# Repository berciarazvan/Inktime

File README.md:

# InkTime

## Prezentarea proiectului

InkTime este un smartwatch open-source, cu cost redus, construit in jurul platformei nRF52840. Proiectul urmeaza cerinta din cadrul cursului de a duce produsul de la stadiul de proiectare electronica pana la o versiune care poate fi fabricata, asamblata si verificata mecanic in carcasa oferita. Repository-ul curent contine schema electrica, layout-ul PCB-ului, fisierele de fabricatie si integrarea 3D necesara pentru etapa EVT.

Designul combina comunicatie wireless, incarcare pentru baterie, monitorizarea bateriei, detectarea miscarii, feedback haptic si interfata pentru un display e-paper pe o placa compacta, adaptata formei carcasei ceasului. Placa a fost dezvoltata ca o solutie pe doua straturi, cu componentele principale plasate pe stratul superior, iar integrarea mecanica a fost verificata in Fusion folosind modelul de carcasa pus la dispozitie.

## Diagrama bloc

```mermaid
flowchart LR
    USB[Conector USB-C] --> ESD[Protectie ESD pentru USB]
    ESD --> CHG[BQ25180 incarcare si management alimentare]
    BAT[Baterie Li-Po] --> CHG
    CHG --> FG[MAX17048 monitorizare baterie]
    CHG --> DCDC[RT6160 convertor buck-boost]
    DCDC --> PWR[Linie principala de 3.3 V]

    PWR --> MCU[nRF52840 microcontroller]
    MCU --> ANT[Antena 2.4 GHz]
    MCU --> IMU[Accelerometru BMA42x]
    MCU --> HAPTIC[Driver haptic DRV2605]
    HAPTIC --> MOTOR[Motor vibratie]
    MCU --> BTN[Trei butoane utilizator]
    MCU --> EPDIF[Interfata logica e-paper]
    EPDIF --> EPDRV[Etaj de comanda e-paper]
    EPDRV --> EPD[Display e-paper]
    MCU --> SWD[Pad-uri programare SWD]
    FG --> MCU
    CHG --> MCU
```

## Bill of Materials

Tabelul de mai jos reprezinta un BOM scurt inclus in README. Fisierele complete pentru fabricatie si asamblare se gasesc in folderul `Manufacturing`. Pentru claritate, tabelul pune accent pe componentele principale si nu pe toate componentele pasive de pe placa.

| Designator | Componenta | Rol in proiect | Link JLC / achizitie | Datasheet |
|---|---|---|---|---|
| U1 | nRF52840-QIAA-R | Microcontroller principal si platforma wireless | [JLCPCB](https://jlcpcb.com/partdetail/NordicSemicon-NRF52840_QIAAR/C190794) | [Nordic Product Specification](https://docs.nordicsemi.com/bundle/nRF52840_PS_v1.9/resource/nRF52840_PS_v1.9.pdf) |
| IC1 | BQ25180YBGR | Incarcator pentru baterie Li-Po si management de alimentare | [JLCPCB](https://jlcpcb.com/partdetail/C3682423) | [Texas Instruments](https://www.ti.com/lit/gpn/BQ25180) |
| IC9 | RT6160AWSC | Convertor buck-boost pentru generarea liniei principale de 3.3 V | [JLCPCB](https://jlcpcb.com/partdetail/C7065276) | [Richtek](https://www.richtek.com/assets/product_file/RT6160A/DS6160A-05.pdf) |
| U3 | MAX17048G+T10 | Circuit de monitorizare a nivelului bateriei | [JLCPCB](https://jlcpcb.com/partdetail/MaximIntegrated-MAX17048GT10/C2682616) | [Analog Devices](https://www.analog.com/media/en/technical-documentation/data-sheets/max17048-max17049.pdf) |
| IC3 | Bosch BMA42x | Accelerometru pentru detectarea miscarii | [JLCPCB search for BMA42x family](https://jlcpcb.com/partdetail/C5242966) | [BMA423 datasheet](https://watchy.sqfmi.com/assets/files/BST-BMA423-DS000-1509600-950150f51058597a6234dd3eaafbb1f0.pdf) |
| IC2 | DRV2605YZFR | Driver haptic pentru actuatorul de vibratie | [JLCPCB](https://jlcpcb.com/partdetail/TexasInstruments-DRV2605YZFR/C81079) | [Texas Instruments](https://www.ti.com/lit/ds/symlink/drv2605.pdf) |
| ANT1 | 2450AT18B100E | Antena chip de 2.4 GHz pentru sectiunea RF | [JLCPCB](https://jlcpcb.com/partdetail/JohansonTechnology-2450AT18B100/C2836414) | [Johanson Technology](https://www.johansontechnology.com/docs/1187/2450AT18B100_X8XXogU.pdf) |
| J4 | KH-TYPE-C-16P | Conector USB-C pentru incarcare si date USB | [JLCPCB](https://jlcpcb.com/partdetail/KH-TYPE-C-16P/C709357) | [Part page with downloadable datasheet](https://jlcpcb.com/partdetail/KH-TYPE-C-16P/C709357) |
| D3 | USBLC6-2SC6Y | Protectie ESD pentru liniile USB | [Reference part page](https://jlcpcb.com/partdetail/ElecSuper-SP2555NUTG_ES/C54533292) | [STMicroelectronics](https://www.st.com/resource/en/datasheet/usblc6-2sc6y.pdf) |
| J1 | 503480-2400 | Conector cu pas fin pentru display-ul e-paper | [Selected connector family](https://www.molex.com/en-us/products/part-detail/5034802400) | [Molex product page](https://www.molex.com/en-us/products/part-detail/5034802400) |
| J2 | TC2030-IDC | Conector extern pentru programare si depanare | [Tag-Connect](https://www.tag-connect.com/product/tc2030-idc-nl) | [Product page](https://www.tag-connect.com/product/tc2030-idc-nl) |

Bateria, panoul e-paper si actuatorul haptic fac de asemenea parte din produsul final, insa in repository-ul curent ele sunt tratate in principal ca elemente de integrare mecanica. Modelele lor 3D sunt incluse in lucrul de asamblare pentru a verifica dispozitivul complet in interiorul carcasei.

## Functionalitatea hardware

Nucleul sistemului este nRF52840, ales pentru ca se potriveste unui dispozitiv purtabil care are nevoie de consum redus, suport wireless integrat si suficiente interfete digitale pentru senzori, controlul display-ului si depanare. In jurul microcontroller-ului, designul pastreaza reteaua RF si antena aproape de marginea placii, iar condensatoarele de decuplare sunt amplasate aproape de pinii de alimentare pentru a mentine sursa stabila.

Sectiunea de alimentare porneste de la conectorul USB-C. Liniile USB sunt protejate de un circuit dedicat de protectie ESD inainte sa ajunga in restul circuitului. Incarcatorul BQ25180 gestioneaza alimentarea de intrare, incarca bateria cu o singura celula si ofera calea de alimentare necesara atunci cand este prezenta tensiunea de la USB. Starea bateriei este monitorizata de MAX17048, astfel incat firmware-ul sa poata estima nivelul de incarcare si sa afiseze aceasta informatie utilizatorului.

Pentru ca sistemul trebuie sa ramana stabil atat atunci cand functioneaza din USB, cat si atunci cand functioneaza din baterie, linia principala este generata de convertorul RT6160. Acest bloc creeaza tensiunea de 3.3 V folosita de partea logica a ceasului. Rezultatul este o alimentare mai stabila pentru microcontroller, senzor, driverul haptic si interfata display-ului.

Detectarea miscarii este realizata cu un accelerometru din familia Bosch BMA42x. Acest dispozitiv comunica cu microcontroller-ul prin magistrala seriala comuna si ofera si linii de intrerupere, ceea ce permite trezirea sistemului sau detectarea unor evenimente de miscare fara interogare continua.

Feedback-ul pentru utilizator este oferit in doua moduri. Primul este vizual, prin conectorul pentru display-ul e-paper si etajul dedicat de comanda al acestuia. Al doilea este tactil, prin driverul DRV2605, care controleaza actuatorul de vibratie. Driverul haptic este conectat pe aceeasi magistrala seriala folosita de celelalte periferice lente, iar un semnal separat de activare permite control clar din partea microcontroller-ului.

Zona dedicata e-paper include atat interfata logica, cat si etajul mic de comanda necesar panoului. Semnalele logice sunt generate de microcontroller, in timp ce etajul analogic extern creeaza tensiunile auxiliare cerute de display. Pe langa conectorul propriu-zis, placa include si un element de comutatie care permite activarea sau dezactivarea ramurii de alimentare a display-ului atunci cand este necesar pentru economisirea energiei.

Trei butoane de utilizator sunt plasate pe placa si aliniate cu butoanele laterale ale carcasei. Fiecare buton este conectat la o intrare dedicata si are o retea pasiva simpla pentru citire stabila. Programarea si depanarea sunt disponibile prin interfata SWD si prin test pad-uri marcate clar, ceea ce usureaza aducerea placii in functiune si validarea.

## Utilizarea pinilor nRF52840

Tabelul de mai jos rezuma principalele conexiuni vizibile in schema incarcata. Scopul acestei sectiuni este sa arate modul in care resursele microcontroller-ului au fost grupate astfel incat designul sa ramana simplu de rutat si usor de urmarit in review.

| Semnal MCU | Functia conectata | Motivul utilizarii |
|---|---|---|
| P0.06 | SDA pentru charger, accelerometru, fuel gauge si driver haptic | O magistrala comuna pentru control reduce complexitatea rutarii si lasa mai multi pini disponibili pentru display si butoane. |
| P0.07 | SCL pentru charger, accelerometru, fuel gauge si driver haptic | Acest pin completeaza magistrala comuna folosita de perifericele de control. |
| P0.08 | IMU interrupt 1 | Aceasta linie permite senzorului sa anunte microcontroller-ul atunci cand apare un eveniment legat de miscare. |
| P1.08 | IMU interrupt 2 | A doua linie de intrerupere ofera flexibilitate pentru functii viitoare si pentru trezire in mod de consum redus. |
| P0.10 | Alerta fuel gauge | Acest semnal poate informa firmware-ul despre evenimente legate de baterie fara interogare constanta. |
| P0.11 | Intrerupere charger | Starea incarcatorului poate fi observata direct de microcontroller, ceea ce ajuta la incarcare si la schimbarile de regim de alimentare. |
| P0.12 | Activare haptic | O linie dedicata ofera control direct asupra sectiunii haptice. |
| P0.02 | Clock serial pentru e-paper | Acest pin este folosit ca linie de ceas pentru interfata de date a display-ului. |
| P0.03 | Date seriale pentru e-paper | Acest pin transporta fluxul de date catre display. |
| P0.05 | Chip select pentru e-paper | Interfata display-ului este separata printr-un semnal dedicat de selectare. |
| P0.15 | Selectare date/comanda pentru e-paper | Aceasta linie diferentiaza comenzile de datele trimise display-ului. |
| P0.16 | Reset pentru e-paper | Display-ul poate fi reinitializat corect prin firmware. |
| P0.17 | Busy pentru e-paper | Microcontroller-ul poate astepta finalizarea operatiilor interne ale panoului inainte de o noua comanda. |
| P1.01 | Control comutare alimentare display | Acest pin comanda poarta MOSFET-ului care activeaza sau dezactiveaza alimentarea display-ului. |
| P0.13 | Intrare buton utilizator | Intrare digitala dedicata pentru unul dintre butoanele ceasului. |
| P0.14 | Intrare buton utilizator | Intrare digitala dedicata pentru unul dintre butoanele ceasului. |
| P1.02 | Intrare buton utilizator | Intrare digitala dedicata pentru al treilea buton al ceasului. |
| D+ / D- / VBUS | Interfata USB nativa | Aceste linii ofera conexiunea USB folosita pentru incarcare si posibila comunicatie pe fir. |
| SWDIO / SWDCLK / P1.00 | Programare si depanare | Aceste semnale permit incarcarea firmware-ului, depanarea si validarea prin SWD si test pad-uri. |

In acest design, liniile display-ului au fost pastrate separat de magistrala comuna de control, astfel incat calea de actualizare a imaginii sa ramana clara si directa. Magistrala comuna a fost rezervata pentru functiile suport, cum sunt incarcarea, monitorizarea bateriei, detectarea miscarii si controlul haptic, ceea ce reprezinta o impartire practica pentru o placa compacta de tip wearable.

## Integrarea PCB-ului si a partii mecanice

Forma PCB-ului urmeaza geometria carcasei si pastreaza antena spre marginea exterioara a placii. Cele trei butoane de utilizator sunt aliniate cu butoanele mecanice din carcasa, iar conectorul USB-C este pozitionat pe marginea placii pentru a ramane accesibil din exterior. Fisierele 3D din repository arata ca placa electronica a fost verificata impreuna cu carcasa pentru confirmarea potrivirii mecanice.

Capturile prezente in proiect pot fi introduse direct in README daca este nevoie. O imagine cu placa in 3D poate fi afisata cu ``, iar o vedere cu placa montata in carcasa poate fi afisata cu ``.

## Decizii de proiectare si observatii pentru review

Acest proiect a fost organizat astfel incat blocurile principale sa ramana usor de verificat in cadrul review-ului. Circuitul de alimentare a fost grupat compact, perifericele de control au fost plasate logic, iar zona RF a fost izolata aproape de marginea cu antena. Au fost adaugate test pad-uri pentru semnalele importante de alimentare si depanare, lucru util atat la aducerea in functiune, cat si in etapa de review.

O decizie practica in acest design a fost impartirea repository-ului in folderele `Hardware`, `Manufacturing`, `Mechanical` si `Images`, deoarece aceasta organizare urmeaza formatul cerut la curs si face proiectul mai usor de inspectat. O alta alegere importanta a fost pregatirea placii nu doar pentru verificare electrica, ci si pentru integrare in carcasa, deoarece validarea finala depinde atat de partea electrica, cat si de cea mecanica.

## Continutul repository-ului

Repository-ul este organizat conform cerintelor cursului. Folderul `Hardware` contine fisierele native pentru schema si PCB, impreuna cu exporturile PDF ale schemei. Folderul `Manufacturing` contine fisierele generate pentru fabricatie si asamblare. Folderul `Mechanical` contine lucrul de integrare in Fusion pentru ansamblul mecanic, iar folderul `Images` contine capturi care documenteaza layout-ul si integrarea in carcasa.

## Concluzie

InkTime este o platforma hardware compacta pentru un smartwatch, construita in jurul unui microcontroller cu consum redus, a unei arhitecturi de alimentare centrate pe baterie si a unui set complet de periferice potrivite pentru utilizare wearable. Versiunea actuala a proiectului include deja fisierele de design, iesirile pentru fabricatie si verificarile mecanice necesare pentru a continua spre validare, review si prezentarea finala.

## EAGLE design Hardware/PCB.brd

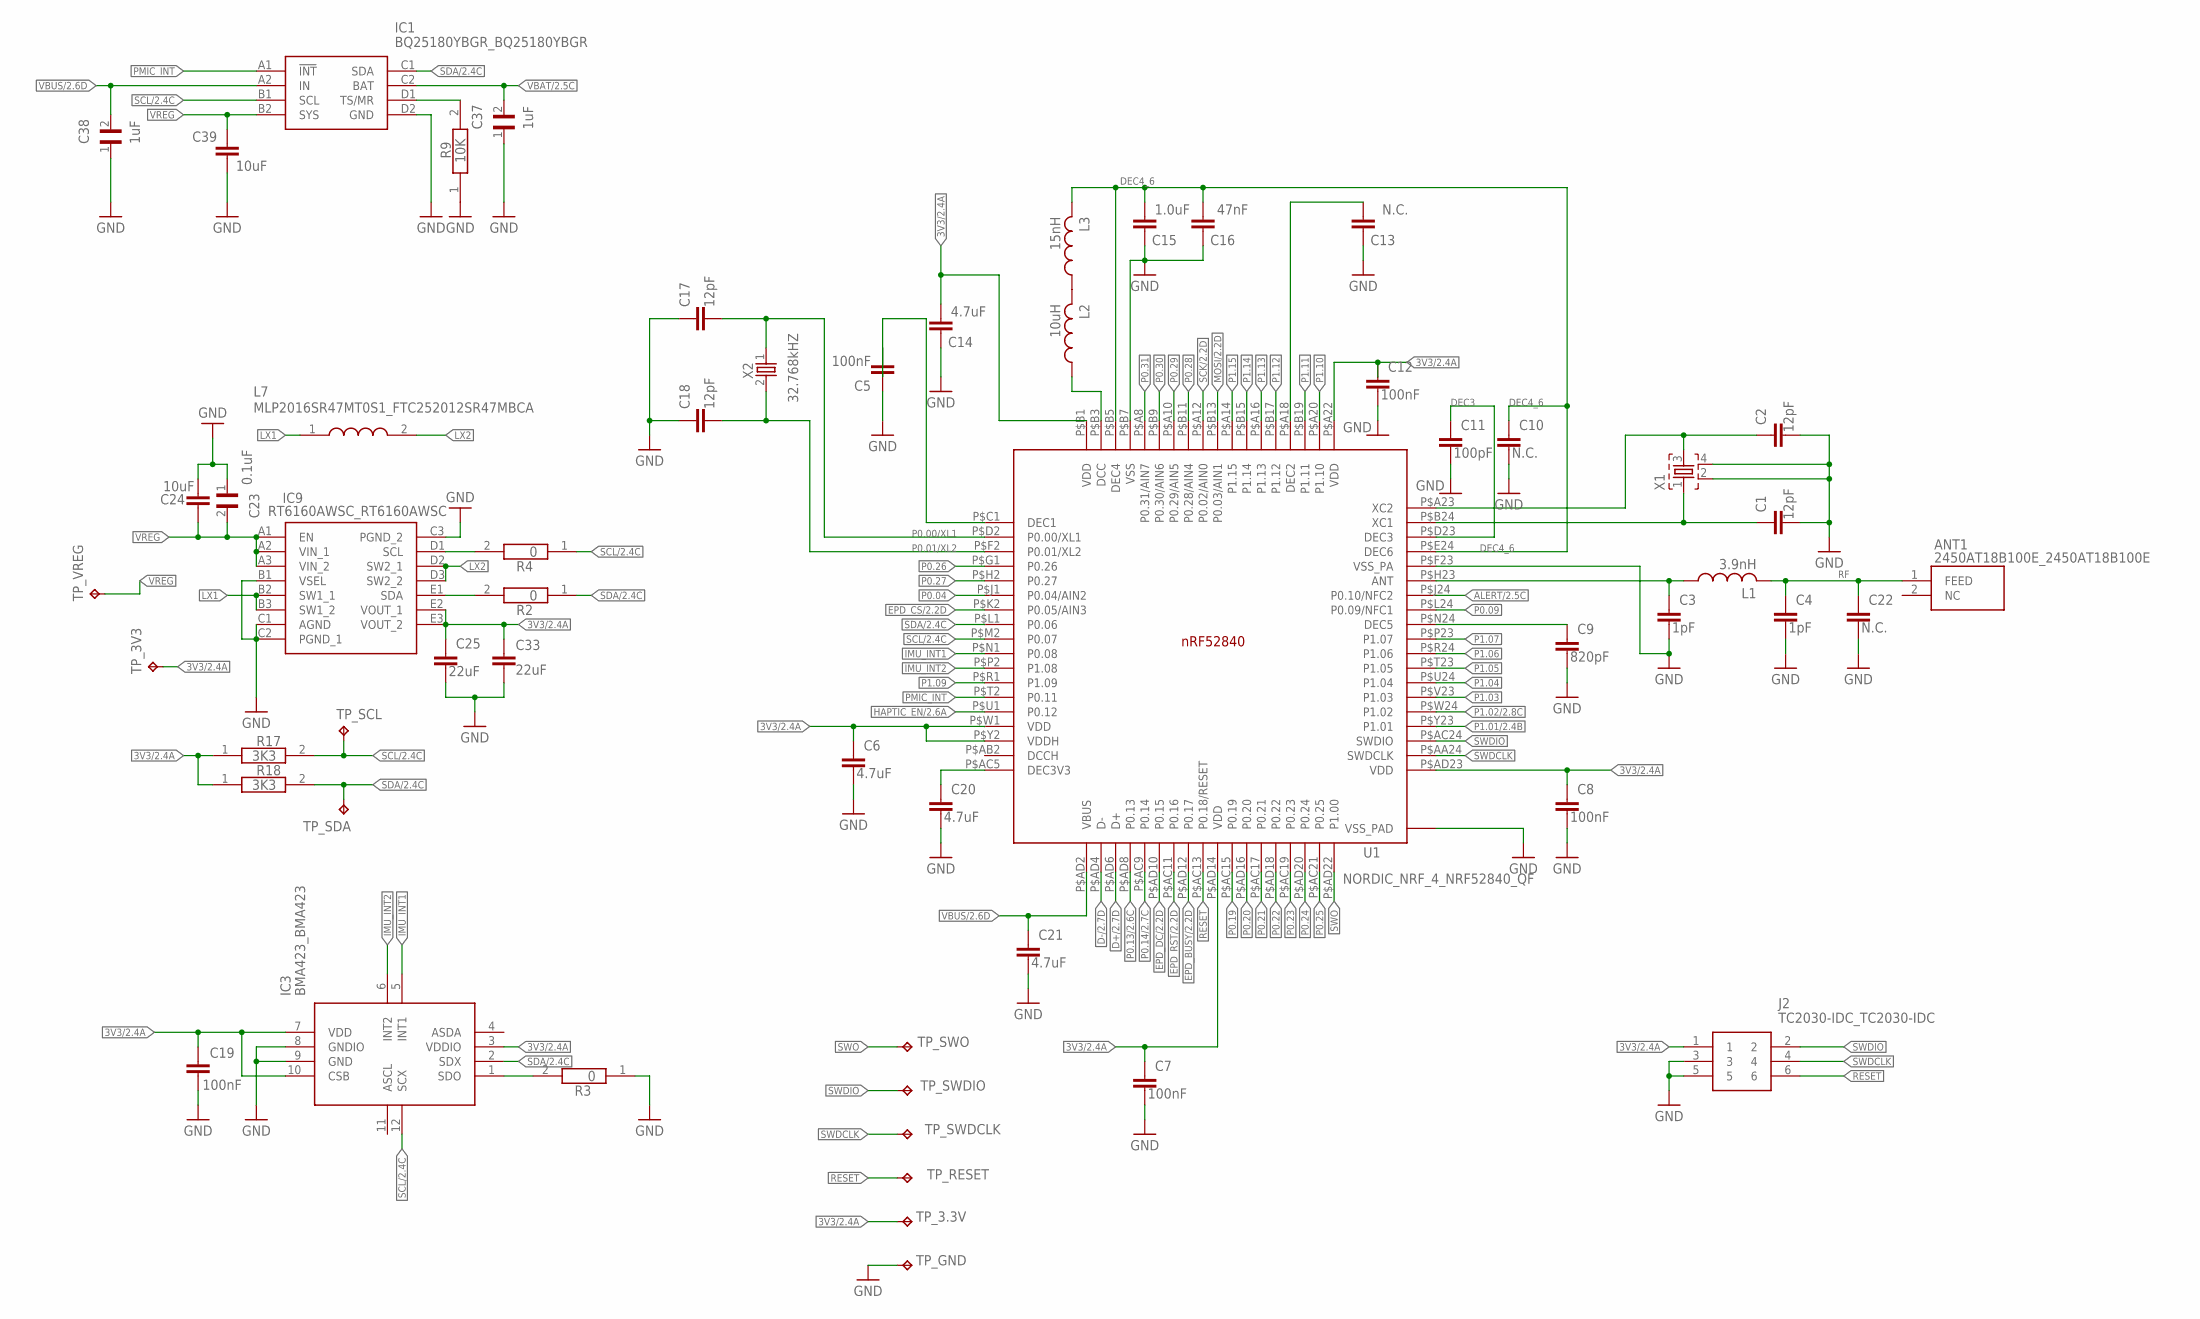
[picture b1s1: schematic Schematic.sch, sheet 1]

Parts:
ANT1: 2450AT18B100E_2450AT18B100E; 2450AT18B100E_ANTC3216X140N
C1, C2, C17, C18: 12pF; NORDIC_NRF_3_RESC0201_L
C3, C4: 1pF; NORDIC_NRF_3_RESC0201_L
C5, C7, C8, C12, C19: 100nF; NORDIC_NRF_3_RESC0201_L
C6, C14, C20, C21: 4.7uF; NORDIC_NRF_3_RESC0201_L
C9: 820pF; NORDIC_NRF_3_RESC0201_L
C10, C13, C22: N.C.; NORDIC_NRF_3_RESC0201_L
C11: 100pF; NORDIC_NRF_3_RESC0201_L
C15: 1.0uF; NORDIC_NRF_3_RESC0201_L
C16: 47nF; NORDIC_NRF_3_RESC0201_L
C23: 0.1uF; GRM011R60J152KE01L_2_CAPC0201X13N
C24, C39: 10uF; NORDIC_NRF_3_RESC0201_L
C25, C33: 22uF; NORDIC_NRF_3_RESC0201_L
C37, C38: 1uF; GRM011R60J152KE01L_1_0201
IC1: BQ25180YBGR_BQ25180YBGR; BQ25180YBGR_BGA8C40P2X4_100X155X50
IC3: BMA423_BMA423
IC9: RT6160AWSC_RT6160AWSC; RT6160AWSC_BGA15C40P3X5_140X230X60
J2: TC2030-IDC_TC2030-IDC; TC2030-IDC_TC2030IDC
L1: 3.9nH; NORDIC_NRF_2_RESC0402_L
L2: 10uH; NORDIC_NRF_2_RESC0402_L
L3: 15nH; NORDIC_NRF_2_RESC0402_L
L7: MLP2016SR47MT0S1_FTC252012SR47MBCA; MLP2016SR47MT0S1_INDC2016X100N
R2, R3, R4: 0; CPF0201D7K68C1_0201
R9: 10K; CPF0201D7K68C1_0201
R17, R18: 3K3; CPF0201D7K68C1_0201
TP_3.3V, TP_3V3: HECTOR_WATCH_1_TPTP20R; HECTOR_WATCH_1_TP20R
TP_GND: HECTOR_WATCH_1_TPTP20R; HECTOR_WATCH_1_TP20R
TP_RESET: HECTOR_WATCH_1_TPTP20R; HECTOR_WATCH_1_TP20R
TP_SCL: HECTOR_WATCH_1_TPTP20R; HECTOR_WATCH_1_TP20R
TP_SDA: HECTOR_WATCH_1_TPTP20R; HECTOR_WATCH_1_TP20R
TP_SWDCLK: HECTOR_WATCH_1_TPTP20R; HECTOR_WATCH_1_TP20R
TP_SWDIO: HECTOR_WATCH_1_TPTP20R; HECTOR_WATCH_1_TP20R
TP_SWO: HECTOR_WATCH_1_TPTP20R; HECTOR_WATCH_1_TP20R
TP_VREG: HECTOR_WATCH_1_TPTP20R; HECTOR_WATCH_1_TP20R
U1: NORDIC_NRF_4_NRF52840_QF; NORDIC_NRF_4_AQFN50P700X700X85_HS-74N
X1: NORDIC_NRF_XTAL_32MHZ; NORDIC_NRF_BT-XTAL_2016_N
X2: 32.768kHZ; NORDIC_NRF_1_XTAL_3215_N

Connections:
3V3/2.4A: C6.1, C7.1, C8.1, C12.1, C14.2, C19.1, IC3.3 (VDDIO), IC3.7 (VDD), IC3.10 (CSB), J2.1, TP_3.3V.TP, TP_3V3.TP, U1.P$A22 (VDD), U1.P$AD14 (VDD), U1.P$AD23 (VDD), U1.P$B1 (VDD), U1.P$W1 (VDD), U1.P$Y2 (VDDH)
ALERT/2.5C: U1.P$J24 (P0.10/NFC2)
D+/2.7D: U1.P$AD6 (D+)
D-/2.7D: U1.P$AD4 (D-)
DEC3: C11.1, U1.P$D23 (DEC3)
DEC4_6: C10.1, C15.2, C16.2, L3.2, U1.P$B5 (DEC4), U1.P$E24 (DEC6)
EPD_BUSY/2.2D: U1.P$AD12 (P0.17)
EPD_CS/2.2D: U1.P$K2 (P0.05/AIN3)
EPD_DC/2.2D: U1.P$AD10 (P0.15)
EPD_RST/2.2D: U1.P$AC11 (P0.16)
GND: C1.2, C2.2, C3.2, C4.2, C5.1, C6.2, C7.2, C8.2, C9.2, C10.2, C11.2, C12.2, C13.1, C14.1, C15.1, C16.1, C17.1, C18.1, C19.2, C20.2, C21.2, C22.2, C23.1, C24.1, C25.2, C33.2, C37.1, C38.1, C39.2, IC1.D2 (GND), IC3.8 (GNDIO), IC3.9 (GND), IC9.B1 (VSEL), IC9.C1 (AGND), IC9.C2 (PGND_1), IC9.C3 (PGND_2), J2.3, J2.5, R3.1, R9.1, TP_GND.TP, U1.P$74 (VSS_PAD), U1.P$75 (VSS_PAD), U1.P$76 (VSS_PAD), U1.P$77 (VSS_PAD), U1.P$78 (VSS_PAD), U1.P$79 (VSS_PAD), U1.P$80 (VSS_PAD), U1.P$81 (VSS_PAD), U1.P$82 (VSS_PAD), U1.P$83 (VSS_PAD), U1.P$84 (VSS_PAD), U1.P$85 (VSS_PAD), U1.P$86 (VSS_PAD), U1.P$87 (VSS_PAD), U1.P$88 (VSS_PAD), U1.P$89 (VSS_PAD), U1.P$90 (VSS_PAD), U1.P$B7 (VSS), U1.P$F23 (VSS_PA), X1.2, X1.4; also elsewhere on the board
HAPTIC_EN/2.6A: U1.P$U1 (P0.12)
IMU_INT1: IC3.5 (INT1), U1.P$N1 (P0.08)
IMU_INT2: IC3.6 (INT2), U1.P$P2 (P1.08)
LX1: IC9.B2 (SW1_1), IC9.B3 (SW1_2), L7.1
LX2: IC9.D2 (SW2_1), IC9.D3 (SW2_2), L7.2
MOSI/2.2D: U1.P$B13 (P0.03/AIN1)
unnamed: IC1.D1 (TS/MR), R9.2
unnamed: C23.2, C24.2, IC9.A1 (EN), IC9.A2 (VIN_1), IC9.A3 (VIN_2)
unnamed: C25.1, C33.1, IC9.E2 (VOUT_1), IC9.E3 (VOUT_2)
unnamed: R17.1, R18.1
unnamed: IC9.D1 (SCL), R4.2
unnamed: IC9.E1 (SDA), R2.2
unnamed: R17.2, TP_SCL.TP
unnamed: R18.2, TP_SDA.TP
unnamed: IC3.1 (SDO), R3.2
unnamed: C20.1, U1.P$AC5 (DEC3V3)
unnamed: C9.1, U1.P$N24 (DEC5)
unnamed: C3.1, L1.1, U1.P$H23 (ANT)
unnamed: C5.2, U1.P$C1 (DEC1)
unnamed: C1.1, U1.P$B24 (XC1), X1.1
unnamed: C2.1, U1.P$A23 (XC2), X1.3
unnamed: L2.1, U1.P$B3 (DCC)
unnamed: L2.2, L3.1
unnamed: C13.2, U1.P$A18 (DEC2)
P0.00/XL1: C17.2, U1.P$D2 (P0.00/XL1), X2.1
P0.01/XL2: C18.2, U1.P$F2 (P0.01/XL2), X2.2
P0.04: U1.P$J1 (P0.04/AIN2)
P0.09: U1.P$L24 (P0.09/NFC1)
P0.13/2.6C: U1.P$AD8 (P0.13)
P0.14/2.7C: U1.P$AC9 (P0.14)
P0.19: U1.P$AC15 (P0.19)
P0.20: U1.P$AD16 (P0.20)
P0.21: U1.P$AC17 (P0.21)
P0.22: U1.P$AD18 (P0.22)
P0.23: U1.P$AC19 (P0.23)
P0.24: U1.P$AD20 (P0.24)
P0.25: U1.P$AC21 (P0.25)
P0.26: U1.P$G1 (P0.26)
P0.27: U1.P$H2 (P0.27)
P0.28: U1.P$B11 (P0.28/AIN4)
P0.29: U1.P$A10 (P0.29/AIN5)
P0.30: U1.P$B9 (P0.30/AIN6)
P0.31: U1.P$A8 (P0.31/AIN7)
P1.01/2.4B: U1.P$Y23 (P1.01)
P1.02/2.8C: U1.P$W24 (P1.02)
P1.03: U1.P$V23 (P1.03)
P1.04: U1.P$U24 (P1.04)
P1.05: U1.P$T23 (P1.05)
P1.06: U1.P$R24 (P1.06)
P1.07: U1.P$P23 (P1.07)
P1.09: U1.P$R1 (P1.09)
P1.10: U1.P$A20 (P1.10)
P1.11: U1.P$B19 (P1.11)
P1.12: U1.P$B17 (P1.12)
P1.13: U1.P$A16 (P1.13)
P1.14: U1.P$B15 (P1.14)
P1.15: U1.P$A14 (P1.15)
PMIC_INT: IC1.A1 (!INT), U1.P$T2 (P0.11)
RESET: J2.6, TP_RESET.TP, U1.P$AC13 (P0.18/RESET)
RF: ANT1.1 (FEED), C4.1, C22.1, L1.2
SCK/2.2D: U1.P$A12 (P0.02/AIN0)
SCL/2.4C: IC1.B1 (SCL), IC3.12 (SCX), U1.P$M2 (P0.07)
SDA/2.4C: IC1.C1 (SDA), IC3.2 (SDX), U1.P$L1 (P0.06)
SWDCLK: J2.4, TP_SWDCLK.TP, U1.P$AA24 (SWDCLK)
SWDIO: J2.2, TP_SWDIO.TP, U1.P$AC24 (SWDIO)
SWO: TP_SWO.TP, U1.P$AD22 (P1.00)
VBAT/2.5C: C37.2, IC1.C2 (BAT)
VBUS/2.6D: C21.1, C38.2, IC1.A2 (IN), U1.P$AD2 (VBUS)
VREG: C39.1, IC1.B2 (SYS), TP_VREG.TP

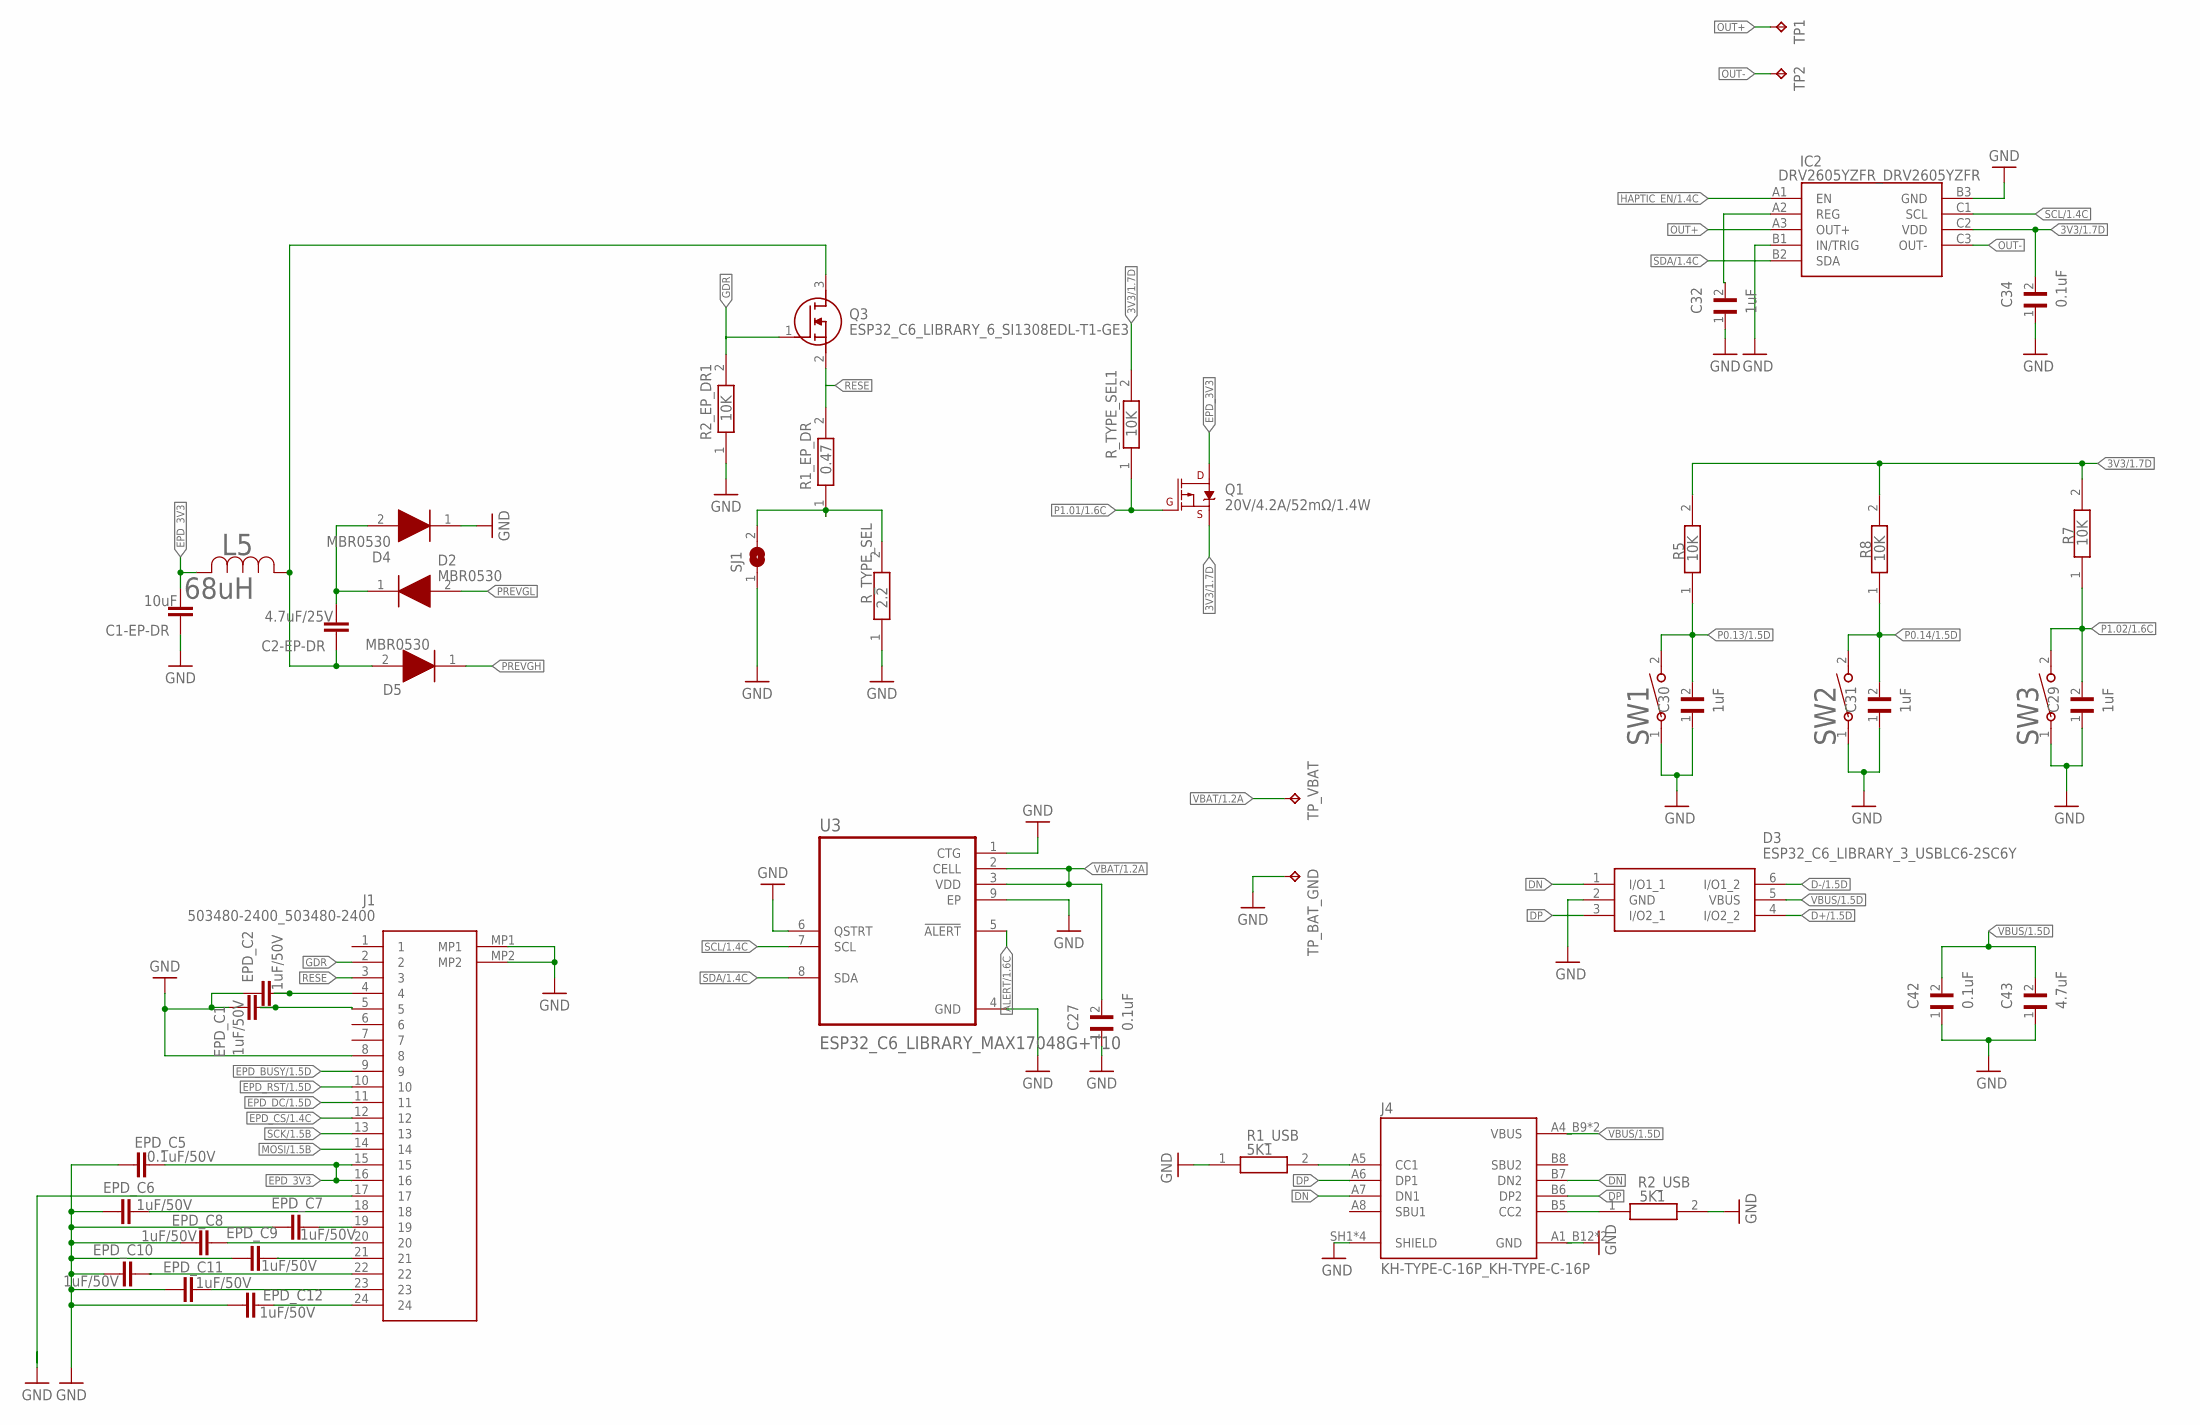
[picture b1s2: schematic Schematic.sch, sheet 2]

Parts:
C1-EP-DR: 10uF; NORDIC_NRF_3_RESC0201_L
C2-EP-DR: 4.7uF/25V; NORDIC_NRF_3_RESC0201_L
C27, C34, C42: 0.1uF; GRM011R60J152KE01L_1_0201
C29, C30, C31, C32: 1uF; GRM011R60J152KE01L_1_0201
C43: 4.7uF; GRM011R60J152KE01L_1_0201
D2, D4, D5: MBR0530; ESP32_C6_LIBRARY_5_SOD3716X135N
D3: ESP32_C6_LIBRARY_3_USBLC6-2SC6Y; ESP32_C6_LIBRARY_3_SOT95P280X145-6N
EPD_C1, EPD_C2, EPD_C6, EPD_C7, EPD_C8, EPD_C9, EPD_C10, EPD_C11, EPD_C12: 1uF/50V; NORDIC_NRF_3_RESC0201_L
EPD_C5: 0.1uF/50V; NORDIC_NRF_3_RESC0201_L
IC2: DRV2605YZFR_DRV2605YZFR; DRV2605YZFR_BGA9C50P3X3_144X144X62
J1: 503480-2400_503480-2400; 503480-2400_5034802400
J4: KH-TYPE-C-16P_KH-TYPE-C-16P; KH-TYPE-C-16P_KINGHELM_KH-TYPE-C-16P
L5: 68uH; ESP32_C6_LIBRARY_2_IND_4828-WE-TPC_WRE
Q1: 20V/4.2A/52mΩ/1.4W; ESP32_C6_LIBRARY_4_ESP32_C6_LIBRARY_4_ESP32_C6_LIBRARY_4_ES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
Q3: ESP32_C6_LIBRARY_6_SI1308EDL-T1-GE3; ESP32_C6_LIBRARY_6_SOT65P210X110-3N
R1_EP_DR: 0.47; CPF0201D7K68C1_0201
R1_USB, R2_USB: 5K1; CPF0201D7K68C1_0201
R2_EP_DR1, R5, R7, R8: 10K; CPF0201D7K68C1_0201
R_TYPE_SEL: 2.2; CPF0201D7K68C1_0201
R_TYPE_SEL1: 10K; CPF0201D7K68C1_0201
SJ1: ESP32_C6_LIBRARY_7_JUMPER_SJ
SW1, SW2, SW3: 2025-10-22_07-23-44_LIBRARY_EVP-AKE31ASW_EVP-AKE3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; 2025-10-22_07-23-44_LIBRARY_SW_EVP-AKE31A_PAN
TP1, TP2: HECTOR_WATCH_1_TPTP20R; HECTOR_WATCH_1_TP20R
TP_BAT_GND: HECTOR_WATCH_1_TPTP20R; HECTOR_WATCH_1_TP20R
TP_VBAT: HECTOR_WATCH_1_TPTP20R; HECTOR_WATCH_1_TP20R
U3: ESP32_C6_LIBRARY_MAX17048G+T10; ESP32_C6_LIBRARY_SON50P200X200X80-9N

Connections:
3V3/1.7D: C34.2, IC2.C2 (VDD), Q1.2 (S), R5.2, R7.2, R8.2, R_TYPE_SEL1.2
ALERT/1.6C: U3.5 (!ALERT)
D+/1.5D: D3.4 (I/O2_2)
D-/1.5D: D3.6 (I/O1_2)
DN: D3.1 (I/O1_1), J4.A7 (DN1), J4.B7 (DN2)
DP: D3.3 (I/O2_1), J4.A6 (DP1), J4.B6 (DP2)
EPD_3V3: C1-EP-DR.2, EPD_C5.2, J1.15, J1.16, L5.2, Q1.3 (D)
EPD_BUSY/1.5D: J1.9
EPD_CS/1.4C: J1.12
EPD_DC/1.5D: J1.11
EPD_RST/1.5D: J1.10
GDR: J1.2, Q3.1 (G), R2_EP_DR1.2
GND: C1-EP-DR.1, C27.1, C29.1, C30.1, C31.1, C32.1, C34.1, C42.1, C43.1, D3.2 (GND), D4.1 (K), EPD_C1.1, EPD_C2.1, EPD_C5.1, EPD_C6.1, EPD_C7.1, EPD_C8.1, EPD_C9.1, EPD_C10.1, EPD_C11.1, EPD_C12.1, IC2.B1 (IN/TRIG), IC2.B3 (GND), J1.8, J1.MP1, J1.MP2, J4.A1_B12 (GND), J4.A12_B1 (GND), J4.SH1 (SHIELD), J4.SH2 (SHIELD), J4.SH3 (SHIELD), J4.SH4 (SHIELD), R1_USB.1, R2_EP_DR1.1, R2_USB.2, R_TYPE_SEL.1, SJ1.1, SW1.1, SW2.1, SW3.1, TP_BAT_GND.TP, U3.1 (CTG), U3.4 (GND), U3.6 (QSTRT), U3.9 (EP); also elsewhere on the board
HAPTIC_EN/1.4C: IC2.A1 (EN)
MOSI/1.5B: J1.14
unnamed: C32.2, IC2.A2 (REG)
unnamed: EPD_C2.2, J1.4
unnamed: EPD_C1.2, J1.5
unnamed: EPD_C6.2, J1.18
unnamed: EPD_C7.2, J1.19
unnamed: EPD_C8.2, J1.20
unnamed: EPD_C9.2, J1.21
unnamed: EPD_C10.2, J1.22
unnamed: EPD_C11.2, J1.23
unnamed: EPD_C12.2, J1.24
unnamed: C2-EP-DR.2, D2.1 (K), D4.2 (A)
unnamed: R1_EP_DR.1, R_TYPE_SEL.2, SJ1.2
unnamed: C2-EP-DR.1, D5.2 (A), L5.1, Q3.3 (D)
unnamed: J4.B5 (CC2), R2_USB.1
unnamed: J4.A5 (CC1), R1_USB.2
OUT+: IC2.A3 (OUT+), TP1.TP
OUT-: IC2.C3 (OUT-), TP2.TP
P0.13/1.5D: C30.2, R5.1, SW1.2
P0.14/1.5D: C31.2, R8.1, SW2.2
P1.01/1.6C: Q1.1 (G), R_TYPE_SEL1.1
P1.02/1.6C: C29.2, R7.1, SW3.2
PREVGH: D5.1 (K)
PREVGL: D2.2 (A)
RESE: J1.3, Q3.2 (S), R1_EP_DR.2
SCK/1.5B: J1.13
SCL/1.4C: IC2.C1 (SCL), U3.7 (SCL)
SDA/1.4C: IC2.B2 (SDA), U3.8 (SDA)
VBAT/1.2A: C27.2, TP_VBAT.TP, U3.2 (CELL), U3.3 (VDD)
VBUS/1.5D: C42.2, C43.2, D3.5 (VBUS), J4.A4_B9 (VBUS), J4.A9_B4 (VBUS)

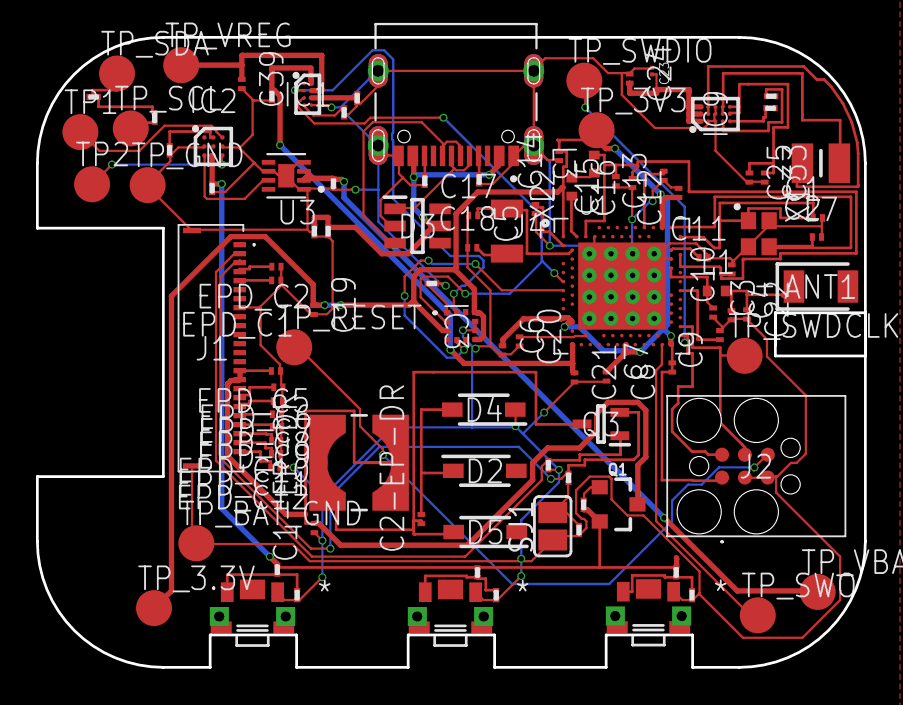
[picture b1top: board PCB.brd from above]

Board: 2 copper layers, 46.0 x 35.0 mm, 105 parts (0 on the bottom side), 70 nets.

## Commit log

2026-04-20 gata
2026-04-21 Create LICENSE

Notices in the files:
parts and their libraries:
COPYRIGHT: Copyright (C) 2024 Ultra Librarian. All rights reserved.
COPYRIGHT: Copyright (C) 2025 Ultra Librarian. All rights reserved.
